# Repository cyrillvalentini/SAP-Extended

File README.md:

# SAP-Extended
Simple-As-Possible Computer based on [Ben Eaters video series](https://www.youtube.com/watch?v=HyznrdDSSGM&list=PLowKtXNTBypGqImE405J2565dvjafglHU&pp=iAQB).
## Project
As part of my matura project, I planned and build an 8-Bit computer based around the design from Ben Eater. This repository contains the schematics, design files and instructions for the computer.

## Breadboard-computer
The breadboard variant is heavily inspired by the computer made by Ben Eater. In the first phase I build computer, which is functionally similar to his design, while occasionally using different parts which were either already on hand or made the process of expanding easier in the future. After a successful test run, I started to expand the design. To allow for longer programs I expanded the RAM to allow 8-Bit addresses and 7-Bit instructions. This allows for a maximum length of 256 instructions. In order to make these changes different modules had to be expanded as well. The other major difference is the expansion port, which allows expansion cards to be created for the computer. The signals are handled by an additional EEPROM-chip within the control logic.

*Simplified diagram of the changes made to the architecture.* 

## Schematics and PCB
After building the breadboard variant, I started working on a PCB version. Being the first larger design, there are some power related issues and some missing filtering components which prevent the computer from running completely. In addition to the breadboard version this design includes a 7-segment display as well as additional power input options. There is an integrated buck converter and an USB Type C port which can supply 5V 3A using PD.

The schematics and PCB were created using KiCad 7.

## Usage

### Programming the computer
To set the computer to programming mode, the clock switch must first be set to manual. The LED should then stop flashing. It is then advisable to press the RESET button once to clear all registers. To be able to program the computer, the programmer must also be plugged in and the RUN/PROGRAM switch must be set to PROGRAM.

Now the actual programming can begin. First, the desired address must be set; without jump commands, these are iterated through in ascending order. In this case, the first command can be saved in the address 00000001. This is followed by the actual command, which can also be entered using the DIP switches. Finally, if the command requires it, the address to be accessed by the command can be entered under "DATA". Once the entire command has been typed in, the "FLASH" button can be pressed. The command should then be displayed in RAM. It is important that the address 00000000 is empty and is not used, as the computer does not always read in the first command after resetting.

### Examples
<center>

| RAM-address| adding two numbers        | show input in output-register |
|------------|---------------------------|-------------------------------|
| 0000 0001  | 0000 0001 0000 1000 (LDA) | 0000 1010 0000 0000 (INA)     |
| 0000 0010  | 0000 0011 0001 0000 (ADD) | 0000 0101 0000 0000 (OUT)     |
| 0000 0011  | 0000 0101 0000 0000 (OUT) | 0000 0110 0000 0001 (JMP)     |
| 0000 0100  | 0000 1100 0000 0000 (HLT) |                               |
| ...        |                           |                               |
| 0000 0100  | 0000 0000 0000 0011 (3)   |                               |
| ...        |                           |                               |
| 0000 0100  | 0000 0000 0000 0001 (1)   |                               |

</center>

### Run a program
To start the program, the switch must be set to RUN. As soon as this has been done, the program can be started either manually by using the button or by switching to automatic mode. For the I/O, it should be noted that the switch next to the display can be used to switch the decimal output between unsigned binary and two's complement. In addition, the input register deletes its contents after use or can be deleted manually using the button next to it. The commands can be found [here](https://github.com/cyrillvalentini/SAP-Extended/blob/main/instructions.pdf)
## Microcode
The control logic is build using AT28C64B parallel EEPROMs, which need to be programmed. The binary file was created using the [txt2bin.py](https://github.com/cyrillvalentini/SAP-Extended/blob/main/microcode/txt2bin.py) python script. The microcode can conveniently be changed as a text file and converted back into a binary image.

The microcode can be flashed to the EEPROMs using crmaykish's [Arduino Mega EEPROM programmer](https://github.com/crmaykish/AT28C-EEPROM-Programmer-Arduino). After hooking everything up as described in the documentation, the EEPROMs can be flashed with their corresponding firmware using following command:

`python.exe .\at28c_programmer.py -d <port> -o 0 -f <microcode.bin> -l 8192 -w`

## Programming port
The modular programming interface allows to use different programmers to load the program into RAM. As of now, there is only a manual programmer that can be used, automatic variants are planned. The interface connects the programmer with a set of multiplexer, which can be controlled using the corresponding switch. By switching to programming mode, the RAM-address as well as the data pins are connected with the pins in the port, which can be accessed by the programmer. There is an additional flash-signal which is hooked up to the write input of the RAM-chips. The full specs of the pins can be found [here](https://github.com/cyrillvalentini/SAP-Extended/blob/main/expansions/programming-port%20specification.pdf).

Note that for entering the programming mode successfully the clock must be set to manual in order to function correctly.

## Expansions
To allow for future expansion both versions of the computer have an expansion port controlled by a dedicated EEPROM within the control logic. There are 16 individual instructions present in the microcode, which can be used to interact with the expansion. The full specifications can be found [here](https://github.com/cyrillvalentini/SAP-Extended/blob/main/expansions/expansion-port%20specification.pdf).

### 8x8 LED-matrix
As of now, the LED-matrix expansion is still in a prototyping phase. Once finished this expansion will allow to display simple graphics which can be copied row by row from either the RAM or the A-register. Combined with the input buttons this will allow the development of simple games, which can be run on the computer. 

*Unfinished prototype of the 8x8 led-matrix*

### Planed expansions
- ALU expansion to allow for additional operations (e.g. logic operations)
- LCD character display
- Automatic programmer

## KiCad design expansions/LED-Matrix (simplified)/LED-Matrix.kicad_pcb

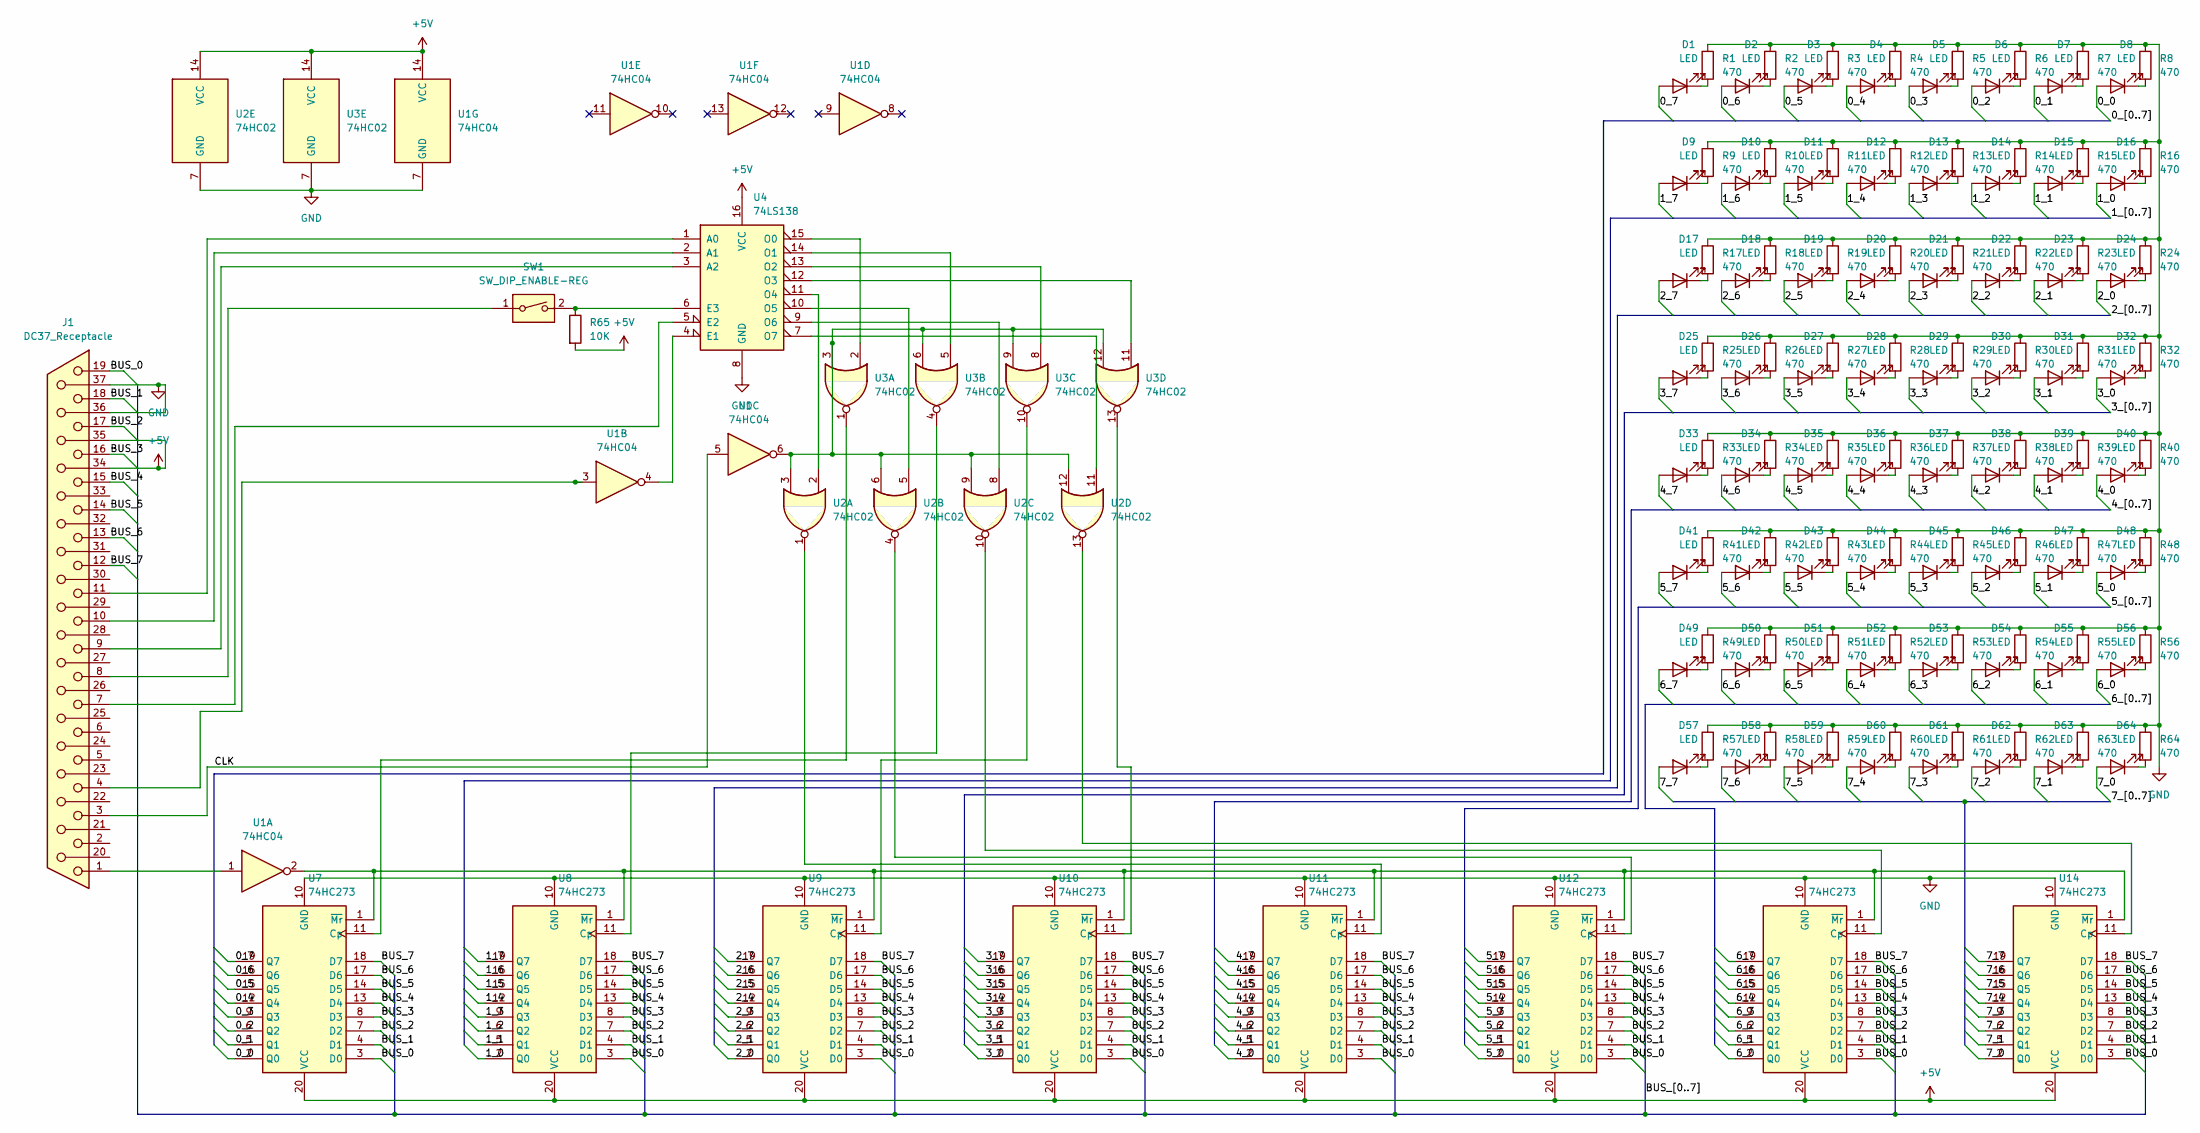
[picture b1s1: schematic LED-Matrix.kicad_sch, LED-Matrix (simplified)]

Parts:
D1, D2, D3, D4, D5, D6, D7, D8, D9, D10, D11, D12, D13, D14, D15, D16, D17, D18, D19, D20, D21, D22, D23, D24, D25, D26, D27, D28, D29, D30, D31, D32, D33, D34, D35, D36, D37, D38, D39, D40, D41, D42, D43, D44, D45, D46, D47, D48, D49, D50, D51, D52, D53, D54, D55, D56, D57, D58, D59, D60, D61, D62, D63, D64: LED; LED_D5.0mm
J1: DC37_Receptacle; DSUB-37_Female_Horizontal_P2.77x2.84mm_EdgePinOffset9.90mm_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
R1, R2, R3, R4, R5, R6, R7, R8, R9, R10, R11, R12, R13, R14, R15, R16, R17, R18, R19, R20, R21, R22, R23, R24, R25, R26, R27, R28, R29, R30, R31, R32, R33, R34, R35, R36, R37, R38, R39, R40, R41, R42, R43, R44, R45, R46, R47, R48, R49, R50, R51, R52, R53, R54, R55, R56, R57, R58, R59, R60, R61, R62, R63, R64: 470; R_1206_3216Metric_Pad1.30x1.75mm_HandSolder
R65: 10K; R_1206_3216Metric_Pad1.30x1.75mm_HandSolder
SW1: SW_DIP_ENABLE-REG; SW_DIP_SPSTx01_Slide_9.78x4.72mm_W7.62mm_P2.54mm
U1: 74HC04; TSSOP-14_4.4x5mm_P0.65mm
U2, U3: 74HC02; TSSOP-14_4.4x5mm_P0.65mm
U4: 74LS138; TSSOP-16_4.4x5mm_P0.65mm
U7, U8, U9, U10, U11, U12, U13, U14: 74HC273; TSSOP-20_4.4x6.5mm_P0.65mm

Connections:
+5V: J1.34, J1.35, R65.2, U1.14 (VCC), U2.14 (VCC), U3.14 (VCC), U4.16 (VCC), U7.20 (VCC), U8.20 (VCC), U9.20 (VCC), U10.20 (VCC), U11.20 (VCC), U12.20 (VCC), U13.20 (VCC), U14.20 (VCC)
/0_0: D8.2 (A), U7.2 (Q0)
/0_1: D7.2 (A), U7.5 (Q1)
/0_2: D6.2 (A), U7.6 (Q2)
/0_3: D5.2 (A), U7.9 (Q3)
/0_4: D4.2 (A), U7.12 (Q4)
/0_5: D3.2 (A), U7.15 (Q5)
/0_6: D2.2 (A), U7.16 (Q6)
/0_7: D1.2 (A), U7.19 (Q7)
/1_0: D16.2 (A), U8.2 (Q0)
/1_1: D15.2 (A), U8.5 (Q1)
/1_2: D14.2 (A), U8.6 (Q2)
/1_3: D13.2 (A), U8.9 (Q3)
/1_4: D12.2 (A), U8.12 (Q4)
/1_5: D11.2 (A), U8.15 (Q5)
/1_6: D10.2 (A), U8.16 (Q6)
/1_7: D9.2 (A), U8.19 (Q7)
/2_0: D24.2 (A), U9.2 (Q0)
/2_1: D23.2 (A), U9.5 (Q1)
/2_2: D22.2 (A), U9.6 (Q2)
/2_3: D21.2 (A), U9.9 (Q3)
/2_4: D20.2 (A), U9.12 (Q4)
/2_5: D19.2 (A), U9.15 (Q5)
/2_6: D18.2 (A), U9.16 (Q6)
/2_7: D17.2 (A), U9.19 (Q7)
/3_0: D32.2 (A), U10.2 (Q0)
/3_1: D31.2 (A), U10.5 (Q1)
/3_2: D30.2 (A), U10.6 (Q2)
/3_3: D29.2 (A), U10.9 (Q3)
/3_4: D28.2 (A), U10.12 (Q4)
/3_5: D27.2 (A), U10.15 (Q5)
/3_6: D26.2 (A), U10.16 (Q6)
/3_7: D25.2 (A), U10.19 (Q7)
/4_0: D40.2 (A), U11.2 (Q0)
/4_1: D39.2 (A), U11.5 (Q1)
/4_2: D38.2 (A), U11.6 (Q2)
/4_3: D37.2 (A), U11.9 (Q3)
/4_4: D36.2 (A), U11.12 (Q4)
/4_5: D35.2 (A), U11.15 (Q5)
/4_6: D34.2 (A), U11.16 (Q6)
/4_7: D33.2 (A), U11.19 (Q7)
/5_0: D48.2 (A), U12.2 (Q0)
/5_1: D47.2 (A), U12.5 (Q1)
/5_2: D46.2 (A), U12.6 (Q2)
/5_3: D45.2 (A), U12.9 (Q3)
/5_4: D44.2 (A), U12.12 (Q4)
/5_5: D43.2 (A), U12.15 (Q5)
/5_6: D42.2 (A), U12.16 (Q6)
/5_7: D41.2 (A), U12.19 (Q7)
/6_0: D56.2 (A), U13.2 (Q0)
/6_1: D55.2 (A), U13.5 (Q1)
/6_2: D54.2 (A), U13.6 (Q2)
/6_3: D53.2 (A), U13.9 (Q3)
/6_4: D52.2 (A), U13.12 (Q4)
/6_5: D51.2 (A), U13.15 (Q5)
/6_6: D50.2 (A), U13.16 (Q6)
/6_7: D49.2 (A), U13.19 (Q7)
/7_0: D64.2 (A), U14.2 (Q0)
/7_1: D63.2 (A), U14.5 (Q1)
/7_2: D62.2 (A), U14.6 (Q2)
/7_3: D61.2 (A), U14.9 (Q3)
/7_4: D60.2 (A), U14.12 (Q4)
/7_5: D59.2 (A), U14.15 (Q5)
/7_6: D58.2 (A), U14.16 (Q6)
/7_7: D57.2 (A), U14.19 (Q7)
/BUS_0: J1.19, U7.3 (D0), U8.3 (D0), U9.3 (D0), U10.3 (D0), U11.3 (D0), U12.3 (D0), U13.3 (D0), U14.3 (D0)
/BUS_1: J1.18, U7.4 (D1), U8.4 (D1), U9.4 (D1), U10.4 (D1), U11.4 (D1), U12.4 (D1), U13.4 (D1), U14.4 (D1)
/BUS_2: J1.17, U7.7 (D2), U8.7 (D2), U9.7 (D2), U10.7 (D2), U11.7 (D2), U12.7 (D2), U13.7 (D2), U14.7 (D2)
/BUS_3: J1.16, U7.8 (D3), U8.8 (D3), U9.8 (D3), U10.8 (D3), U11.8 (D3), U12.8 (D3), U13.8 (D3), U14.8 (D3)
/BUS_4: J1.15, U7.13 (D4), U8.13 (D4), U9.13 (D4), U10.13 (D4), U11.13 (D4), U12.13 (D4), U13.13 (D4), U14.13 (D4)
/BUS_5: J1.14, U7.14 (D5), U8.14 (D5), U9.14 (D5), U10.14 (D5), U11.14 (D5), U12.14 (D5), U13.14 (D5), U14.14 (D5)
/BUS_6: J1.13, U7.17 (D6), U8.17 (D6), U9.17 (D6), U10.17 (D6), U11.17 (D6), U12.17 (D6), U13.17 (D6), U14.17 (D6)
/BUS_7: J1.12, U7.18 (D7), U8.18 (D7), U9.18 (D7), U10.18 (D7), U11.18 (D7), U12.18 (D7), U13.18 (D7), U14.18 (D7)
/CLK: J1.3, U1.5
GND: J1.36, J1.37, R1.1, R2.1, R3.1, R4.1, R5.1, R6.1, R7.1, R8.1, R9.1, R10.1, R11.1, R12.1, R13.1, R14.1, R15.1, R16.1, R17.1, R18.1, R19.1, R20.1, R21.1, R22.1, R23.1, R24.1, R25.1, R26.1, R27.1, R28.1, R29.1, R30.1, R31.1, R32.1, R33.1, R34.1, R35.1, R36.1, R37.1, R38.1, R39.1, R40.1, R41.1, R42.1, R43.1, R44.1, R45.1, R46.1, R47.1, R48.1, R49.1, R50.1, R51.1, R52.1, R53.1, R54.1, R55.1, R56.1, R57.1, R58.1, R59.1, R60.1, R61.1, R62.1, R63.1, R64.1, U1.7 (GND), U2.7 (GND), U3.7 (GND), U4.8 (GND), U7.10 (GND), U8.10 (GND), U9.10 (GND), U10.10 (GND), U11.10 (GND), U12.10 (GND), U13.10 (GND), U14.10 (GND)
unnamed: D1.1 (K), R1.2
unnamed: D2.1 (K), R2.2
unnamed: D3.1 (K), R3.2
unnamed: D4.1 (K), R4.2
unnamed: D5.1 (K), R5.2
unnamed: D6.1 (K), R6.2
unnamed: D7.1 (K), R7.2
unnamed: D8.1 (K), R8.2
unnamed: D9.1 (K), R9.2
unnamed: D10.1 (K), R10.2
unnamed: D11.1 (K), R11.2
unnamed: D12.1 (K), R12.2
unnamed: D13.1 (K), R13.2
unnamed: D14.1 (K), R14.2
unnamed: D15.1 (K), R15.2
unnamed: D16.1 (K), R16.2
unnamed: D17.1 (K), R17.2
unnamed: D18.1 (K), R18.2
unnamed: D19.1 (K), R19.2
unnamed: D20.1 (K), R20.2
unnamed: D21.1 (K), R21.2
unnamed: D22.1 (K), R22.2
unnamed: D23.1 (K), R23.2
unnamed: D24.1 (K), R24.2
unnamed: D25.1 (K), R25.2
unnamed: D26.1 (K), R26.2
unnamed: D27.1 (K), R27.2
unnamed: D28.1 (K), R28.2
unnamed: D29.1 (K), R29.2
unnamed: D30.1 (K), R30.2
unnamed: D31.1 (K), R31.2
unnamed: D32.1 (K), R32.2
unnamed: D33.1 (K), R33.2
unnamed: D34.1 (K), R34.2
unnamed: D35.1 (K), R35.2
unnamed: D36.1 (K), R36.2
unnamed: D37.1 (K), R37.2
unnamed: D38.1 (K), R38.2
unnamed: D39.1 (K), R39.2
unnamed: D40.1 (K), R40.2
unnamed: D41.1 (K), R41.2
unnamed: D42.1 (K), R42.2
unnamed: D43.1 (K), R43.2
unnamed: D44.1 (K), R44.2
unnamed: D45.1 (K), R45.2
unnamed: D46.1 (K), R46.2
unnamed: D47.1 (K), R47.2
unnamed: D48.1 (K), R48.2
unnamed: D49.1 (K), R49.2
unnamed: D50.1 (K), R50.2
unnamed: D51.1 (K), R51.2
unnamed: D52.1 (K), R52.2
unnamed: D53.1 (K), R53.2
unnamed: D54.1 (K), R54.2
unnamed: D55.1 (K), R55.2
unnamed: D56.1 (K), R56.2
unnamed: D57.1 (K), R57.2
unnamed: D58.1 (K), R58.2
unnamed: D59.1 (K), R59.2
unnamed: D60.1 (K), R60.2
unnamed: D61.1 (K), R61.2
unnamed: D62.1 (K), R62.2
unnamed: D63.1 (K), R63.2
unnamed: D64.1 (K), R64.2
unnamed: J1.1, U1.1
unnamed: J1.4, U1.3
unnamed: J1.8, SW1.1
unnamed: U1.6, U2.3, U2.6, U2.9, U2.12, U3.3, U3.6, U3.9, U3.12
unnamed: J1.11, U4.1 (A0)
unnamed: J1.10, U4.2 (A1)
unnamed: J1.9, U4.3 (A2)
unnamed: U1.4, U4.4 (E1)
unnamed: J1.7, U4.5 (E2)
unnamed: R65.1, SW1.2, U4.6 (E3)
unnamed: U3.2, U4.15 (O0)
unnamed: U3.5, U4.14 (O1)
unnamed: U3.8, U4.13 (O2)
unnamed: U3.11, U4.12 (O3)
unnamed: U2.2, U4.11 (O4)
unnamed: U2.5, U4.10 (O5)
unnamed: U2.8, U4.9 (O6)
unnamed: U2.11, U4.7 (O7)
unnamed: U3.1, U7.11 (Cp)
unnamed: U3.4, U8.11 (Cp)
unnamed: U3.10, U9.11 (Cp)
unnamed: U3.13, U10.11 (Cp)
unnamed: U1.2, U7.1 (~Mr), U8.1 (~Mr), U9.1 (~Mr), U10.1 (~Mr), U11.1 (~Mr), U12.1 (~Mr), U13.1 (~Mr), U14.1 (~Mr)
unnamed: U2.1, U11.11 (Cp)
unnamed: U2.4, U12.11 (Cp)
unnamed: U2.10, U13.11 (Cp)
unnamed: U2.13, U14.11 (Cp)

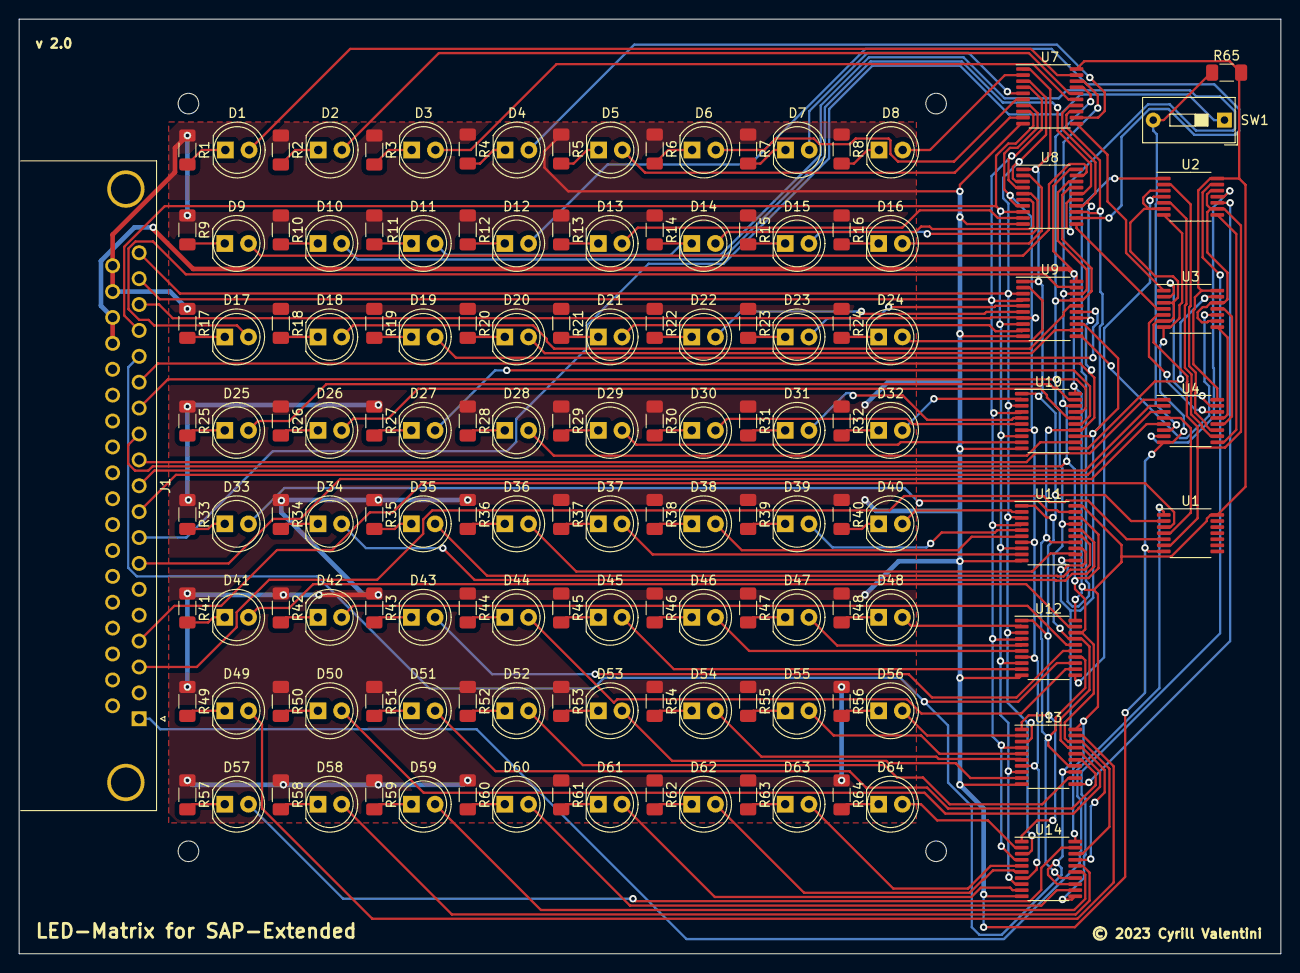
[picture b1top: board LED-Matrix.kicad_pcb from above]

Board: 2 copper layers, 135.0 x 100.0 mm, 143 parts (0 on the bottom side), 166 nets.

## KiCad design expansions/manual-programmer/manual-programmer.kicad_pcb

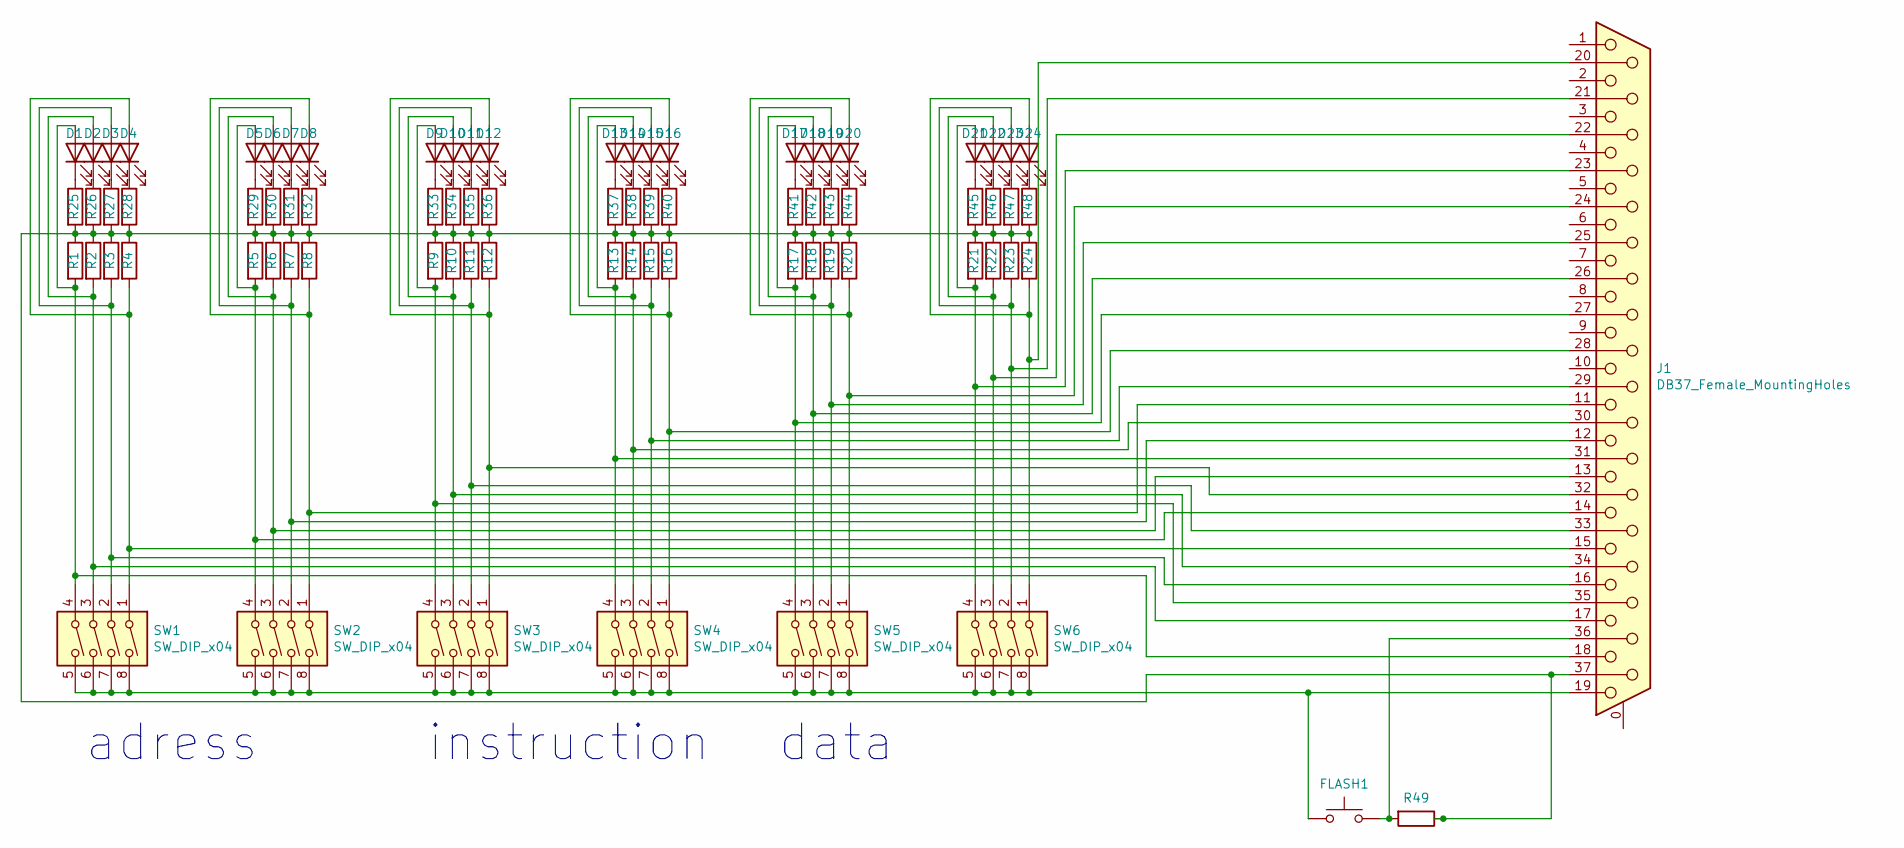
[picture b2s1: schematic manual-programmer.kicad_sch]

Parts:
D1, D2, D3, D4, D5, D6, D7, D8, D9, D10, D11, D12, D13, D14, D15, D16, D17, D18, D19, D20, D21, D22, D23, D24: LED; LED_D5.0mm
FLASH1: SW_Push; SW_PUSH_6mm
J1: DB37_Female_MountingHoles; DSUB-37_Female_Horizontal_P2.77x2.84mm_EdgePinOffset7.70mm_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
R1, R2, R3, R4, R5, R6, R7, R8, R9, R10, R11, R12, R13, R14, R15, R16, R17, R18, R19, R20, R21, R22, R23, R24: 10K; R_1206_3216Metric_Pad1.30x1.75mm_HandSolder
R25, R26, R27, R28, R29, R30, R31, R32, R33, R34, R35, R36, R37, R38, R39, R40, R41, R42, R43, R44, R45, R46, R47, R48: 470; R_1206_3216Metric_Pad1.30x1.75mm_HandSolder
R49: 1K; R_1206_3216Metric_Pad1.30x1.75mm_HandSolder
SW1, SW2, SW3, SW4, SW5, SW6: SW_DIP_x04; SW_DIP_SPSTx04_Slide_9.78x12.34mm_W7.62mm_P2.54mm

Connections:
unnamed: D1.2 (A), J1.18, R1.2, SW1.4
unnamed: D1.1 (K), R25.1
unnamed: D2.2 (A), J1.17, R2.2, SW1.3
unnamed: D2.1 (K), R26.1
unnamed: D3.2 (A), J1.16, R3.2, SW1.2
unnamed: D3.1 (K), R27.1
unnamed: D4.2 (A), J1.15, R4.2, SW1.1
unnamed: D4.1 (K), R28.1
unnamed: D5.2 (A), J1.14, R5.2, SW2.4
unnamed: D5.1 (K), R29.1
unnamed: D6.2 (A), J1.13, R6.2, SW2.3
unnamed: D6.1 (K), R30.1
unnamed: D7.2 (A), J1.12, R7.2, SW2.2
unnamed: D7.1 (K), R31.1
unnamed: D8.2 (A), J1.11, R8.2, SW2.1
unnamed: D8.1 (K), R32.1
unnamed: D9.2 (A), J1.35, R9.2, SW3.4
unnamed: D9.1 (K), R33.1
unnamed: D10.2 (A), J1.34, R10.2, SW3.3
unnamed: D10.1 (K), R34.1
unnamed: D11.2 (A), J1.33, R11.2, SW3.2
unnamed: D11.1 (K), R35.1
unnamed: D12.2 (A), J1.32, R12.2, SW3.1
unnamed: D12.1 (K), R36.1
unnamed: D13.2 (A), J1.31, R13.2, SW4.4
unnamed: D13.1 (K), R37.1
unnamed: D14.2 (A), J1.30, R14.2, SW4.3
unnamed: D14.1 (K), R38.1
unnamed: D15.2 (A), J1.29, R15.2, SW4.2
unnamed: D15.1 (K), R39.1
unnamed: D16.2 (A), J1.28, R16.2, SW4.1
unnamed: D16.1 (K), R40.1
unnamed: D17.2 (A), J1.27, R17.2, SW5.4
unnamed: D17.1 (K), R41.1
unnamed: D18.2 (A), J1.26, R18.2, SW5.3
unnamed: D18.1 (K), R42.1
unnamed: D19.2 (A), J1.25, R19.2, SW5.2
unnamed: D19.1 (K), R43.1
unnamed: D20.2 (A), J1.24, R20.2, SW5.1
unnamed: D20.1 (K), R44.1
unnamed: D21.2 (A), J1.23, R21.2, SW6.4
unnamed: D21.1 (K), R45.1
unnamed: D22.2 (A), J1.22, R22.2, SW6.3
unnamed: D22.1 (K), R46.1
unnamed: D23.2 (A), J1.21, R23.2, SW6.2
unnamed: D23.1 (K), R47.1
unnamed: D24.2 (A), J1.20, R24.2, SW6.1
unnamed: D24.1 (K), R48.1
unnamed: FLASH1.1, J1.19, SW1.5, SW1.6, SW1.7, SW1.8, SW2.5, SW2.6, SW2.7, SW2.8, SW3.5, SW3.6, SW3.7, SW3.8, SW4.5, SW4.6, SW4.7, SW4.8, SW5.5, SW5.6, SW5.7, SW5.8, SW6.5, SW6.6, SW6.7, SW6.8
unnamed: FLASH1.2, J1.36, R49.2
unnamed: J1.37, R1.1, R2.1, R3.1, R4.1, R5.1, R6.1, R7.1, R8.1, R9.1, R10.1, R11.1, R12.1, R13.1, R14.1, R15.1, R16.1, R17.1, R18.1, R19.1, R20.1, R21.1, R22.1, R23.1, R24.1, R25.2, R26.2, R27.2, R28.2, R29.2, R30.2, R31.2, R32.2, R33.2, R34.2, R35.2, R36.2, R37.2, R38.2, R39.2, R40.2, R41.2, R42.2, R43.2, R44.2, R45.2, R46.2, R47.2, R48.2, R49.1

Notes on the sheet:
adress
data
instruction

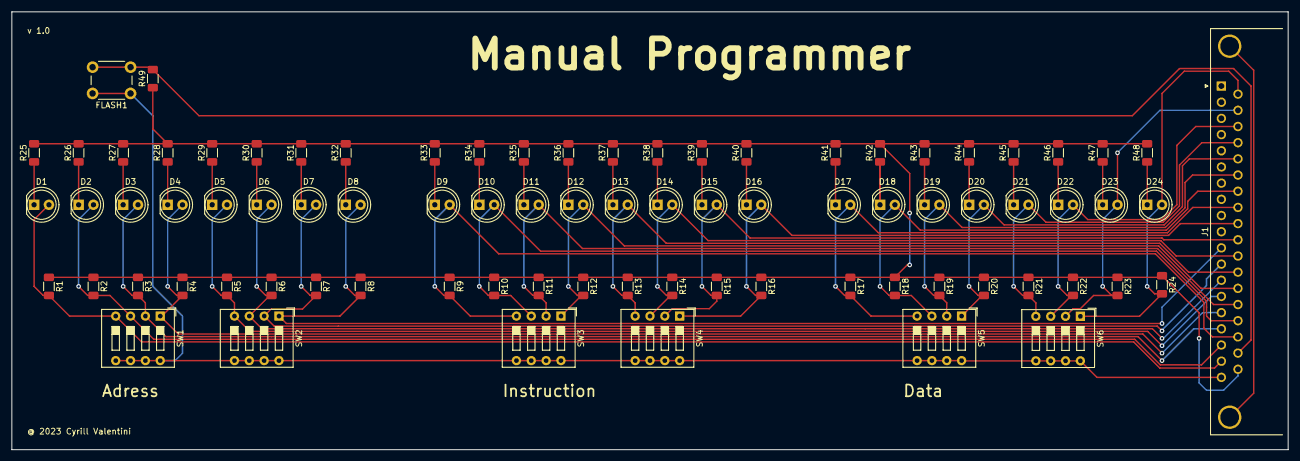
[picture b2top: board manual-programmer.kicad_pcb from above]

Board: 2 copper layers, 218.4 x 74.9 mm, 81 parts (0 on the bottom side), 51 nets.

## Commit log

2023-11-03 uploading files, more cleanup needs to happen soon
2023-11-03 added images for future illustration
2023-11-03 Update README.md
    image test
2023-11-03 moved bom.html
2023-11-14 translation of instructions
2023-11-15 exported translated pdf files
2023-11-15 modified README.md
2023-11-17 added more info the the README file
2023-12-01 changed wrong image in README.md
2023-12-01 updatd README.md

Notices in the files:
expansions/LED-Matrix (simplified)/LED-Matrix.kicad_pcb:
© 2023 Cyrill Valentini
